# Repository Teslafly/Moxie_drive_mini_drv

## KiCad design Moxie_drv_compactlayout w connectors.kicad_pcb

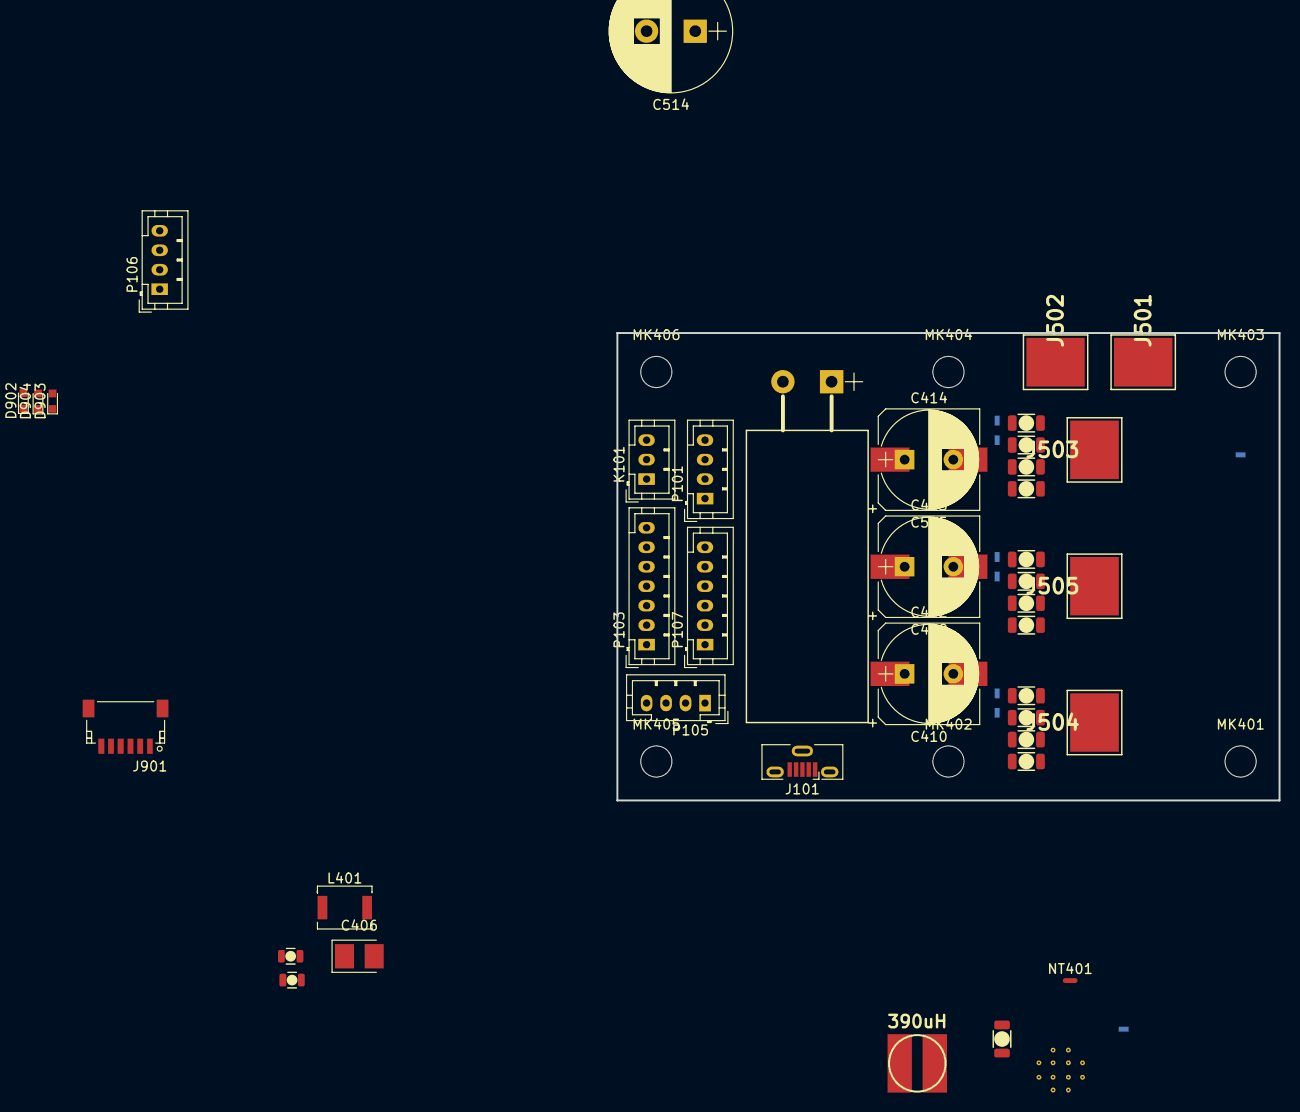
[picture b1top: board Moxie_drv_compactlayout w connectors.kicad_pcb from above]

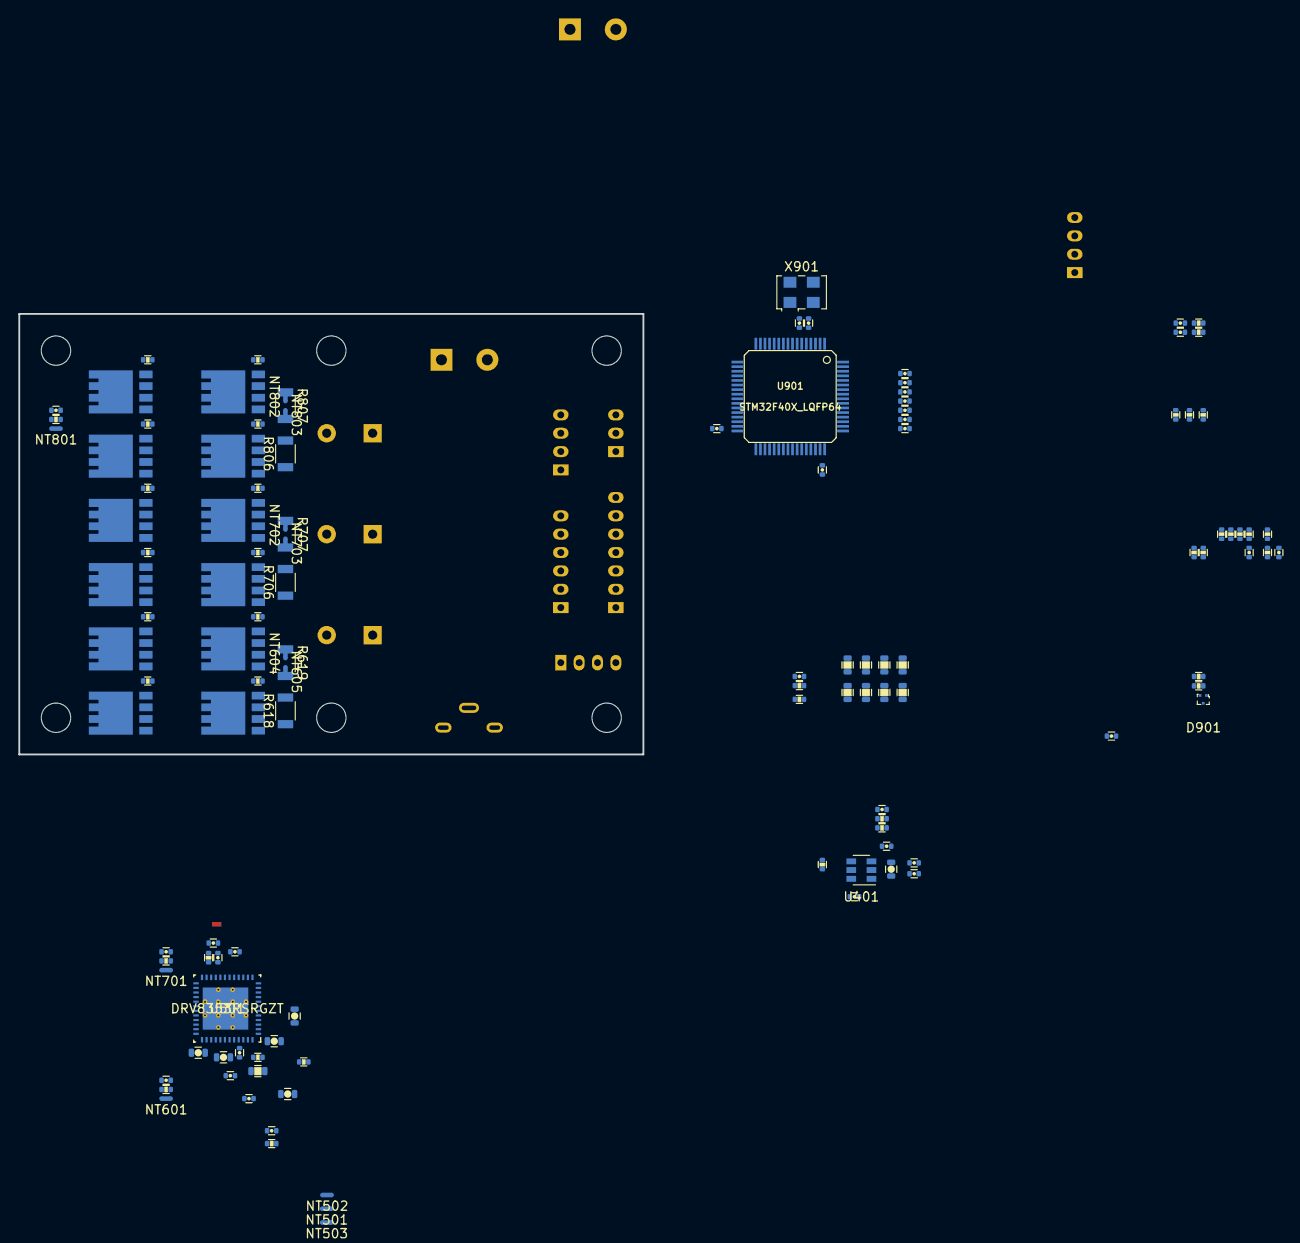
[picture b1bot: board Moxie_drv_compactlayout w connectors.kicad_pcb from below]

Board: 4 copper layers, 68.0 x 48.0 mm, 170 parts (121 on the bottom side), 110 nets, no tracks yet.

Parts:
C101, C107, C904: 100n; C_0402
C201: 4.7nf; C_0402
C202, C901, C902, C903, C905, C907, C909, C910, C911, C912: 2.2u; C_0402
C401: 2.2uf; C_0603
C402, C403, C404, C408: 100nf; C_0402
C405: 2.2uf; C_0402
C406: 100uf; CP_Tantalum_Case-B_EIA-3528-21_Reflow
C407: NP; C_0402
C409, C410, C515: 20uF; CP_Elec_10x10.5
C411: 560uF; CP_Radial_D12.5mm_P5.00mm_horiz
C412, C413, C414: 56uF; CP_Radial_D10.0mm_P5.00mm
C501: 10uF; C_0805
C502: 1.5uF; C_1206
C503, C504: 0.1uF; C_0603
C505: 0.47uF; C_0402
C506: 0.1uF; C_0402
C507: 0.047uF; C_0402
C508, C509, C511: 1uF; C_0603
C510: 0.01uF; C_0402
C512: 18nF; C_0402
C513: 22uF; C_0805
C514: 560uF; CP_Radial_D12.5mm_P5.00mm
C601, C701, C801: 2.2nF; C_0402
C602, C603, C604, C606, C702, C703, C704, C706, C802, C803, C804, C806: 1uF; C_1206
C906, C908: 15p; C_0402
D901: TPD2EUSB30DRTR; SOT-3
D902: BLUE; LED_0603
D903: GREEN; LED_0603
D904: RED; LED_0603
J101: USB_B_Micro; USB_Micro-B_Vertical_Molex-105133-0001
J501: +Vbat; 1PAD_6x5mm
J502: Gnd; 1PAD_6x5mm
J503: A; 1PAD_6x5mm
J504: B; 1PAD_6x5mm
J505: C; 1PAD_6x5mm
J901: SWD; JST_SH_SM06B-SRSS-TB_06x1.00mm_Angled
K101: SERVO; JST_PH_B3B-PH-K_03x2.00mm_Straight
L401: 3.3uH; L_Neosid_Ms42
L501: 390uH; inductor_smd_5.8mmx4.8hmm
MK401, MK402, MK403, MK404, MK405, MK406: Mounting_Hole; MountingHole_3.2mm_M3_DIN965
NT401, NT501, NT502, NT503, NT601, NT604, NT605, NT701, NT702, NT703, NT801, NT802, NT803: Net-Tie_2; NetTie-2_SMD_Pad0.5mm
P101: CANBUS; JST_PH_B4B-PH-K_04x2.00mm_Straight
P103: CTRL_SIGNALS; JST_PH_B7B-PH-K_07x2.00mm_Straight
P105: Serial1/tim4; JST_PH_B4B-PH-K_04x2.00mm_Straight
P106: I2C; JST_PH_B4B-PH-K_04x2.00mm_Straight
P107: HALL/Encoder; JST_PH_B6B-PH-K_06x2.00mm_Straight
Q601, Q602, Q603, Q604, Q701, Q702, Q703, Q704, Q801, Q802, Q803, Q804: TPH2R608NH,L1Q; SOP8_Advance
R101: 0Ω; R_0402
R102, R603, R703, R803: 100Ω; R_0402
R103, R104: 100kΩ; R_0402
R105, R106: 22R; R_0402
R107, R108, R109: 2k2Ω; R_0402
R110, R516: 10kΩ; R_0402
R201, R202: 120R; R_0402
R401, R901, R902, R903: 1k; R_0402
R402: R33.2k 0.1%; R_0402
R403: 10k 0.1%; R_0402
R501: 1kOhm; C_0402
R502: 10kΩ; C_0402
R503: 560kΩ; R_0402
R504: 200kΩ; R_0402
R505: 5.1kΩ; R_0402
R506: 1.0kΩ; R_0402
R507: 910mΩ; R_0603
R508, R510, R512, R514: 47kΩ; R_0603
R509, R511, R513, R515: 2.2kΩ; R_0603
R517: NTC 10kΩ; R_0402
R601, R602, R604, R605, R701, R702, R704, R705, R801, R802, R804, R805: 5Ω; R_0402
R618, R619, R706, R707, R806, R807: 1mΩ; R_1206
U401: TPS561201; SOT-23-6
U501: DRV8353RSRGZT; DRV8353RHRGZR
U901: STM32F40X_LQFP64; lqfp64_pad_mod
X901: 8MHz 10ppm; Oscillator_SMD_EuroQuartz_XO53-4pin_5.0x3.2mm

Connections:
+3V3: C202.1, C404.1, C405.1, C406.1, C407.1, C902.2, C905.2, C907.2, C909.2, C910.2, C911.2, C912.2, J901.1, L401.1, NT503.2, P103.1, P105.3, P106.3, P107.1, R101.2, R107.2, R108.2, R109.2, R110.2, R402.1, R501.1, R502.1, R516.1, R901.2, U901.1, U901.13, U901.19, U901.32, U901.48, U901.64
+12V: C401.1, C402.1, C501.1, C503.1, C513.1, R401.2, R507.2, U401.3, U501.5
+BATT: C409.1, C410.1, C411.1, C412.1, C413.1, C414.1, C502.1, C504.1, C514.1, C515.1, C602.1, C603.1, C604.1, C606.1, C702.1, C703.1, C704.1, C706.1, C802.1, C803.1, C804.1, C806.1, J501.1, NT401.1, Q601.1, Q603.1, Q701.1, Q703.1, Q801.1, Q803.1, R503.1, R514.1, U501.43
/CAN_tranciever/CANH: P101.3, R201.1
/CAN_tranciever/CANL: P101.2, R202.1
/Microcontroller/ADC_BRAKE: P103.4, R104.1, U901.27
/Microcontroller/ADC_TEMP: C408.1, R516.2, R517.1, U901.24
/Microcontroller/ADC_THROTTLE: P103.3, R103.1, U901.26
/Microcontroller/ADC_VBUS: R514.2, R515.1, U901.11
/Microcontroller/BRAKE_SW: P103.6, U901.57
/Microcontroller/FAULT: R502.2, U501.28, U901.33
/Microcontroller/H1: U501.34, U901.41
/Microcontroller/H2: U501.36, U901.42
/Microcontroller/H3: U501.38, U901.43
/Microcontroller/HALL_1: P107.3, R107.1, U901.37
/Microcontroller/HALL_2: P107.4, R108.1, U901.38
/Microcontroller/HALL_3: P107.5, R109.1, U901.39
/Microcontroller/L1: U501.35, U901.34
/Microcontroller/L2: U501.37, U901.35
/Microcontroller/L3: U501.39, U901.36
/Microcontroller/LED_GREEN: R902.2, U901.3
/Microcontroller/LED_RED: R903.2, U901.4
/Microcontroller/SCL_2: P106.1, U901.29
/Microcontroller/SDA_2: P106.2, U901.30
/Microcontroller/SERVO: C101.2, R102.1, U901.17
/Microcontroller/TEMP_MOTOR: C107.2, P107.2, R110.1, U901.25
/Microcontroller/USART1_RX: P105.1, U901.59
/Microcontroller/USART1_TX: P105.2, U901.58
/Microcontroller/USB_DM: D901.2, R106.1, U901.44
/Microcontroller/USB_DP: D901.1, R105.1, U901.45
/Microcontroller/VCAP1: C903.2, U901.31
/Microcontroller/VCAP2: C901.2, U901.47
/drv_power_stage/3.3_IREF: C506.1, NT503.1, U501.26
/drv_power_stage/A_ISENSE: U501.25, U901.8
/drv_power_stage/A_VSENSE: R508.2, R509.1, U901.14
/drv_power_stage/B_ISENSE: U501.24, U901.9
/drv_power_stage/B_VSENSE: R510.2, R511.1, U901.15
/drv_power_stage/C_ISENSE: U501.23, U901.10
/drv_power_stage/C_VSENSE: R512.2, R513.1, U901.16
/drv_power_stage/DRV_SDO: R501.2, U501.29
/drv_power_stage/ENABLE: U501.33, U901.40
/drv_power_stage/GDRV_VSENSE: C512.1, R505.2, R506.1, U501.48
/drv_power_stage/PHASE_A: J503.1, NT801.2, Q801.3, Q802.1, Q803.3, Q804.1, R508.1
/drv_power_stage/PHASE_B: J504.1, NT601.2, Q601.3, Q602.1, Q603.3, Q604.1, R510.1
/drv_power_stage/PHASE_C: J505.1, NT701.2, Q701.3, Q702.1, Q703.3, Q704.1, R512.1
/drv_power_stage/buck_rcl: R504.2, U501.46
/drv_power_stage/power_phase_A/H_GATE: R801.2, R804.2, U501.8
/drv_power_stage/power_phase_A/H_SWITCH: NT801.1, U501.9
/drv_power_stage/power_phase_A/L_GATE: R802.2, R805.2, U501.10
/drv_power_stage/power_phase_A/NR_SENSE: C801.1, R803.1, U501.12
/drv_power_stage/power_phase_A/PH_GND_LOW: NT802.2, Q802.3, Q804.3, R806.1, R807.1
/drv_power_stage/power_phase_A/PR_SENSE: C801.2, NT802.1, U501.11
/drv_power_stage/power_phase_B/H_GATE: R601.2, R604.2, U501.17
/drv_power_stage/power_phase_B/H_SWITCH: NT601.1, U501.16
/drv_power_stage/power_phase_B/L_GATE: R602.2, R605.2, U501.15
/drv_power_stage/power_phase_B/NR_SENSE: C601.1, R603.1, U501.13
/drv_power_stage/power_phase_B/PH_GND_LOW: NT604.2, Q602.3, Q604.3, R618.1, R619.1
/drv_power_stage/power_phase_B/PR_SENSE: C601.2, NT604.1, U501.14
/drv_power_stage/power_phase_C/H_GATE: R701.2, R704.2, U501.18
/drv_power_stage/power_phase_C/H_SWITCH: NT701.1, U501.19
/drv_power_stage/power_phase_C/L_GATE: R702.2, R705.2, U501.20
/drv_power_stage/power_phase_C/NR_SENSE: C701.1, R703.1, U501.22
/drv_power_stage/power_phase_C/PH_GND_LOW: NT702.2, Q702.3, Q704.3, R706.1, R707.1
/drv_power_stage/power_phase_C/PR_SENSE: C701.2, NT702.1, U501.21
GND: C101.1, C107.1, C201.2, C202.2, C401.2, C402.2, C404.2, C405.2, C406.2, C409.2, C410.2, C411.2, C412.2, C413.2, C414.2, C514.2, C515.2, C901.1, C903.1, C904.1, C906.2, C907.1, C908.2, C909.1, C910.1, C911.1, C912.1, D901.3, D902.2, D903.2, D904.2, J101.5, J101.6, J502.1, J901.3, K101.3, NT501.2, NT502.2, P101.1, P103.2, P103.7, P105.4, P106.4, P107.6, R103.2, R104.2, R403.2, U401.1, U501.41, U901.18, U901.60, U901.63, X901.3
GNDA: C408.2, C506.2, C902.1, C905.1, NT501.1, U501.27, U901.12
GNDD: C501.2, C502.2, C503.2, C504.2, C505.2, C508.1, C509.2, C513.2, C602.2, C603.2, C604.2, C606.2, C702.2, C703.2, C704.2, C706.2, C802.2, C803.2, C804.2, C806.2, NT502.1, NT605.2, NT703.2, NT803.2, R504.1, R506.2, R509.2, R511.2, R513.2, R515.2, R517.2, R618.2, R619.2, R706.2, R707.2, R806.2, R807.2, U501.1, U501.49
NRST: C904.2, J901.5, U901.7
unnamed: C201.1, R201.2, R202.2
unnamed: C403.1, L401.2, U401.2
unnamed: C403.2, U401.6
unnamed: C407.2, R402.2, R403.1, U401.4
unnamed: C505.1, U501.44
unnamed: C507.1, U501.4
unnamed: C507.2, U501.3
unnamed: C508.2, U501.2
unnamed: C509.1, U501.40
unnamed: C510.1, U501.45
unnamed: C510.2, L501.2, U501.42
unnamed: C511.1, NT401.2, U501.6
unnamed: C511.2, U501.7
unnamed: C512.2, L501.1, R505.1, R507.1
unnamed: C906.1, U901.5, X901.1
unnamed: C908.1, U901.6, X901.2
unnamed: D902.1, R901.1
unnamed: D903.1, R902.1
unnamed: D904.1, R903.1
unnamed: J101.2, R106.2
unnamed: J101.3, R105.2
unnamed: K101.1, R102.2
unnamed: K101.2, R101.1
unnamed: NT605.1, R603.2
unnamed: NT703.1, R703.2
unnamed: NT803.1, R803.2
unnamed: Q601.2, R601.1
unnamed: Q602.2, R602.1
unnamed: Q603.2, R604.1
unnamed: Q604.2, R605.1
unnamed: Q701.2, R701.1
unnamed: Q702.2, R702.1
unnamed: Q703.2, R704.1
unnamed: Q704.2, R705.1
unnamed: Q801.2, R801.1
unnamed: Q802.2, R802.1
unnamed: Q803.2, R804.1
unnamed: Q804.2, R805.1
unnamed: R401.1, U401.5
unnamed: R503.2, U501.47
SWCLK: J901.2, U901.49
SWDIO: J901.4, U901.46

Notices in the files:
parts and their libraries:
Copyright 2016 Accelerated Designs. All rights reserved.
